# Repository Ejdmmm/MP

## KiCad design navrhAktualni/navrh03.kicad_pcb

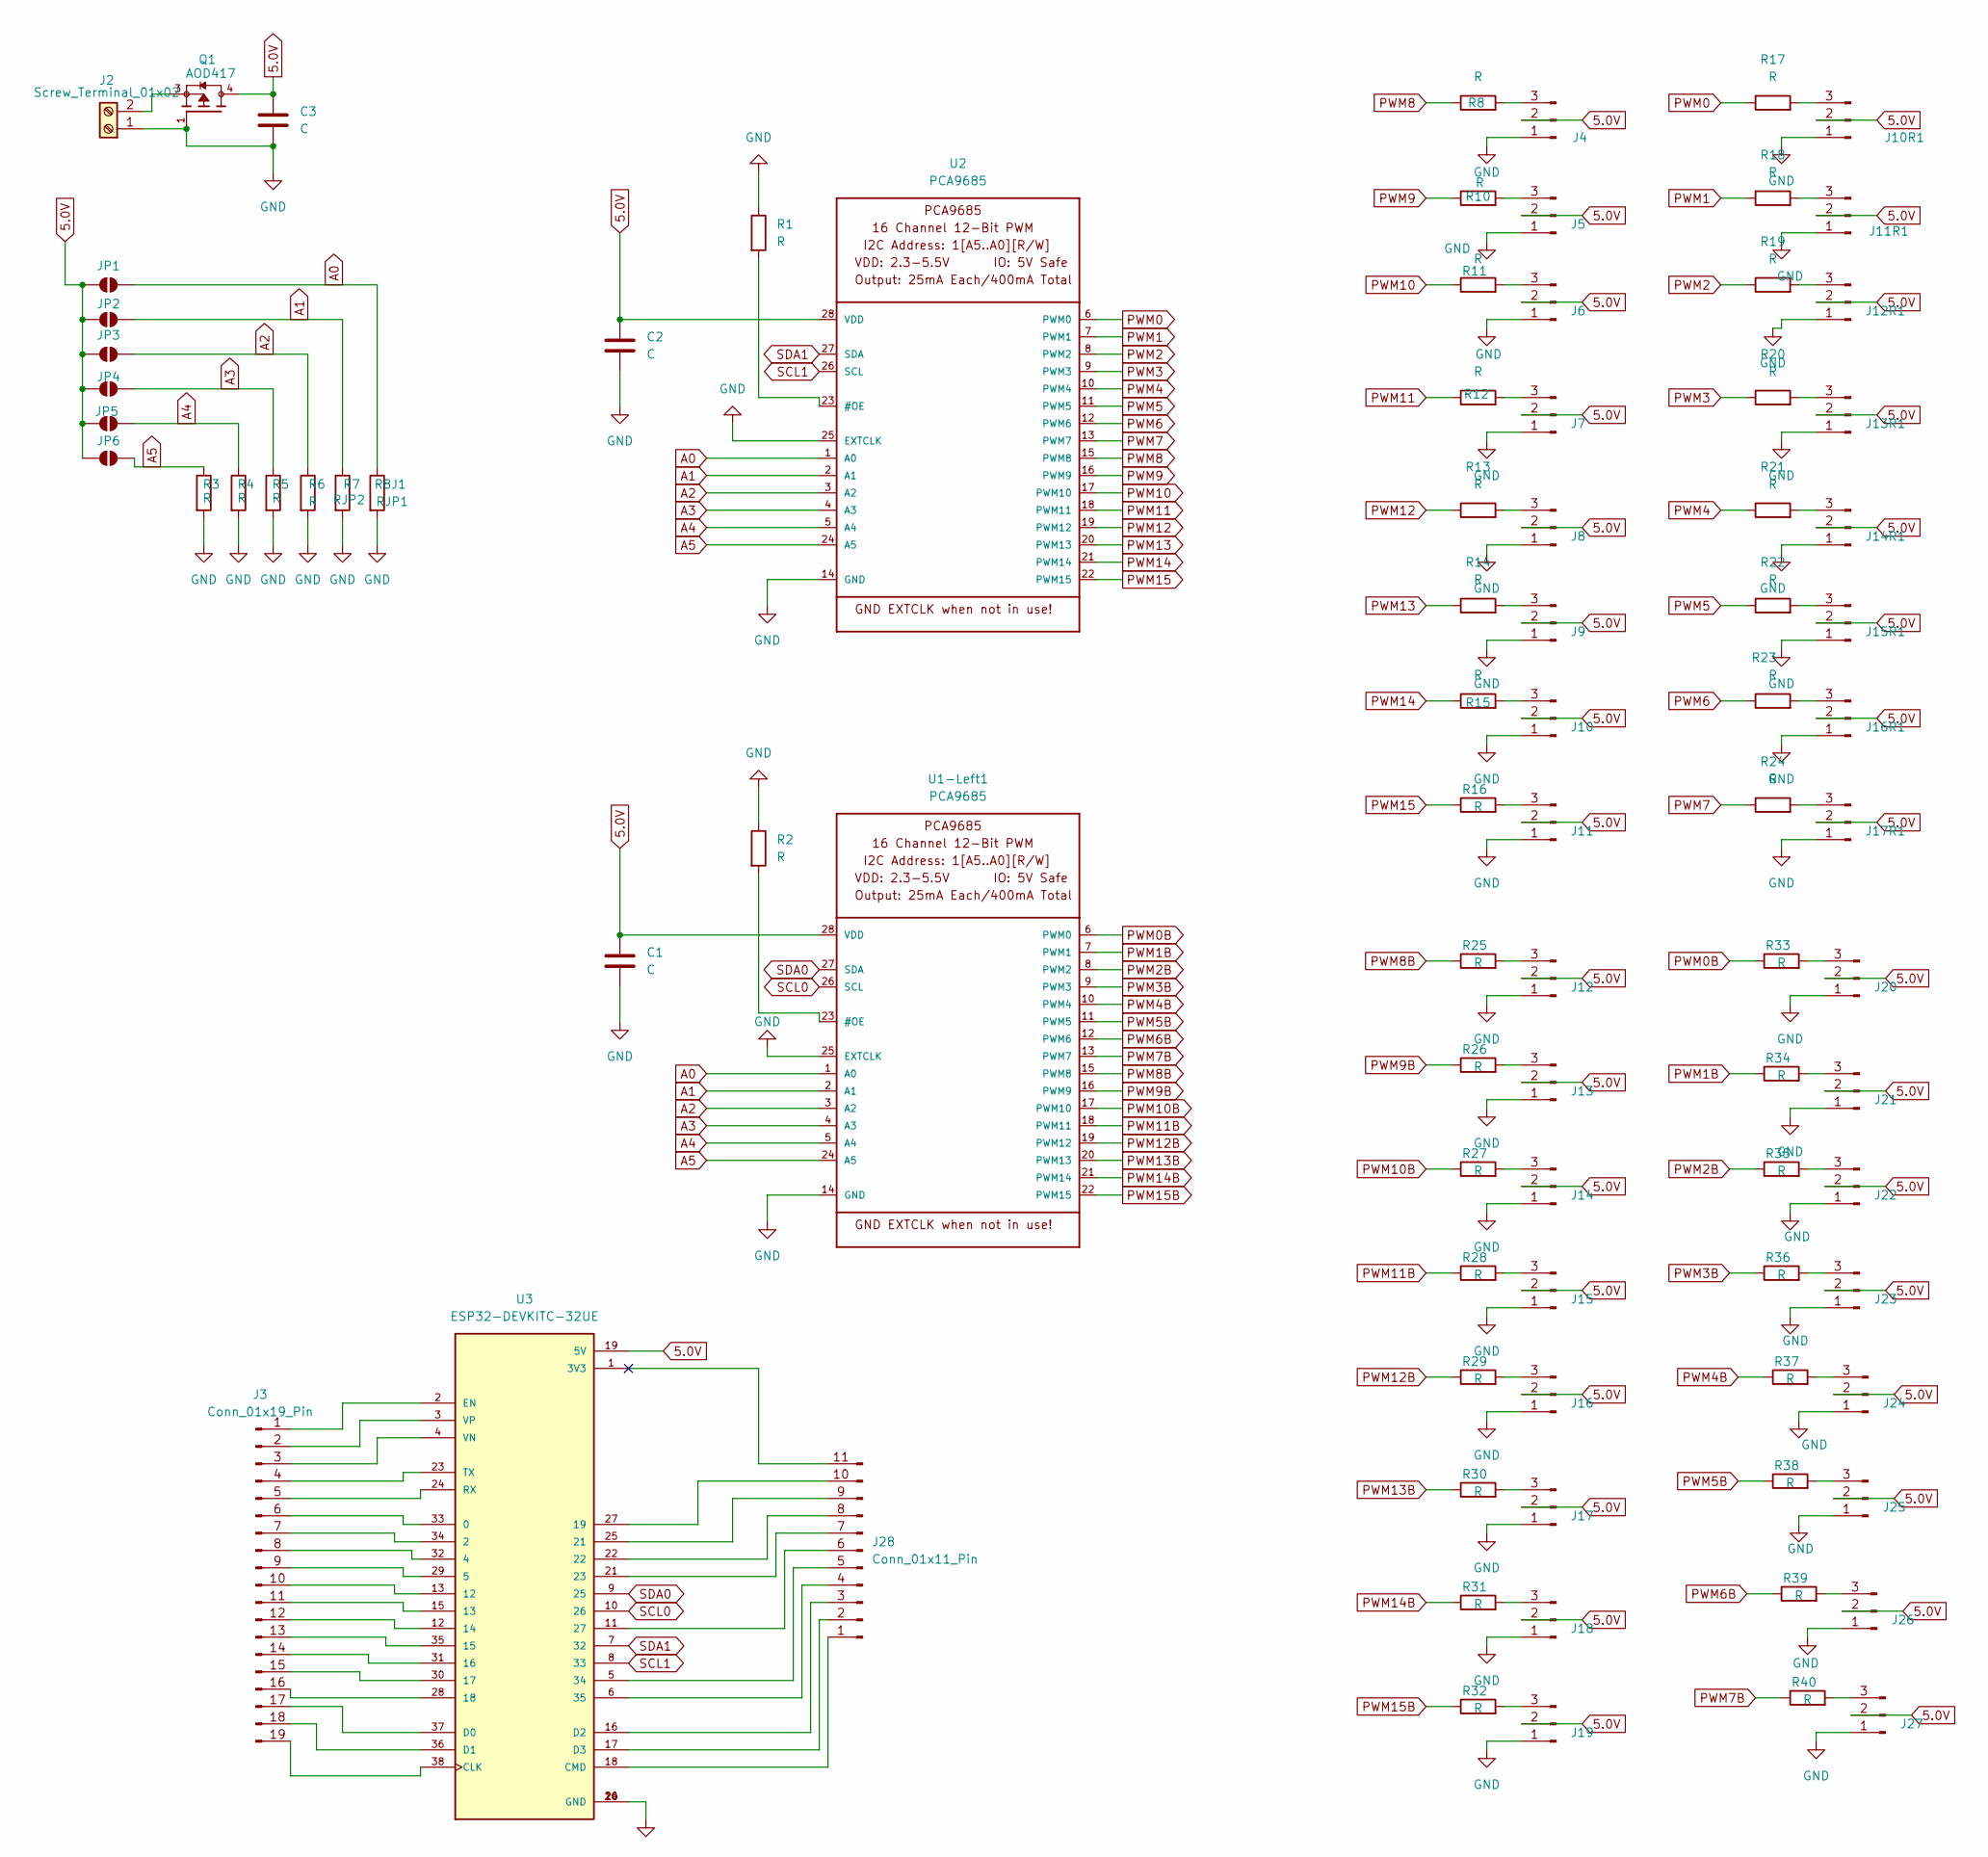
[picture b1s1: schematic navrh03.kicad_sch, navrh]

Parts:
C1: C; C_Disc_D7.5mm_W5.0mm_P7.50mm
C2, C3: C; CP_EIA-1608-08_AVX-J
J2: Screw_Terminal_01x02; PinHeader_1x02_P2.00mm_Vertical
J3: Conn_01x19_Pin; PinHeader_1x19_P2.00mm_Vertical
J4, J5, J6, J7, J8, J9, J10, J10R1, J11, J11R1, J12, J12R1, J13, J13R1, J14, J14R1, J15, J15R1, J16, J16R1, J17, J17R1, J18, J19, J20, J21, J22, J23, J24, J25, J26, J27: Conn_01x03_Pin; PinHeader_1x03_P2.00mm_Vertical
J28: Conn_01x11_Pin; PinHeader_1x11_P2.00mm_Vertical
JP1, JP2, JP3, JP4, JP5, JP6: SolderJumper_2_Open; SolderJumper-2_P1.3mm_Open_Pad1.0x1.5mm
Q1: AOD417; DPAK228P994X240_3N; PARTREV U
R1, R2, R3, R4, R5, R6, R8, R10, R11, R12, R13, R14, R15, R16, R17, R18, R19, R20, R21, R22, R23, R24, R25, R26, R27, R28, R29, R30, R31, R32, R33, R34, R35, R36, R37, R38, R39, R40: R; R_0201_0603Metric
R7: RJP2; R_0201_0603Metric
R8J1: RJP1; R_0201_0603Metric
U1-Left1, U2: PCA9685; TSSOP28
U3: ESP32-DEVKITC-32UE; ESPRESSIF_ESP32-DEVKITC-32UE; PARTREV V4

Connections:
A0: JP1.2 (B), R8J1.1, U1-Left1.1 (A0), U2.1 (A0)
A1: JP2.2 (B), R7.1, U1-Left1.2 (A1), U2.2 (A1)
A2: JP3.2 (B), R6.1, U1-Left1.3 (A2), U2.3 (A2)
A3: JP4.2 (B), R5.1, U1-Left1.4 (A3), U2.4 (A3)
A4: JP5.2 (B), R4.1, U1-Left1.5 (A4), U2.5 (A4)
A5: JP6.2 (B), R3.1, U1-Left1.24 (A5), U2.24 (A5)
unnamed: J2.2, Q1.3
unnamed: J3.1, U3.2 (EN)
unnamed: J3.2, U3.3 (VP)
unnamed: J3.3, U3.4 (VN)
unnamed: J3.4, U3.23 (TX)
unnamed: J3.5, U3.24 (RX)
unnamed: J3.6, U3.33 (0)
unnamed: J3.7, U3.34 (2)
unnamed: J3.8, U3.32 (4)
unnamed: J3.9, U3.29 (5)
unnamed: J3.10, U3.13 (12)
unnamed: J3.11, U3.15 (13)
unnamed: J3.12, U3.12 (14)
unnamed: J3.13, U3.35 (15)
unnamed: J3.14, U3.31 (16)
unnamed: J3.15, U3.30 (17)
unnamed: J3.16, U3.28 (18)
unnamed: J3.17, U3.37 (D0)
unnamed: J3.18, U3.36 (D1)
unnamed: J3.19, U3.38 (CLK)
unnamed: J4.3, R8.2
unnamed: J5.3, R10.2
unnamed: J6.3, R11.2
unnamed: J7.3, R12.2
unnamed: J8.3, R13.2
unnamed: J9.3, R14.2
unnamed: J10.3, R15.2
unnamed: J10R1.3, R17.2
unnamed: J11.3, R16.2
unnamed: J11R1.3, R18.2
unnamed: J12.3, R25.2
unnamed: J12R1.3, R19.2
unnamed: J13.3, R26.2
unnamed: J13R1.3, R20.2
unnamed: J14.3, R27.2
unnamed: J14R1.3, R21.2
unnamed: J15.3, R28.2
unnamed: J15R1.3, R22.2
unnamed: J16.3, R29.2
unnamed: J16R1.3, R23.2
unnamed: J17.3, R30.2
unnamed: J17R1.3, R24.2
unnamed: J18.3, R31.2
unnamed: J19.3, R32.2
unnamed: J20.3, R33.2
unnamed: J21.3, R34.2
unnamed: J22.3, R35.2
unnamed: J23.3, R36.2
unnamed: J24.3, R37.2
unnamed: J25.3, R38.2
unnamed: J26.3, R39.2
unnamed: J27.3, R40.2
unnamed: J28.1, U3.18 (CMD)
unnamed: J28.2, U3.17 (D3)
unnamed: J28.3, U3.16 (D2)
unnamed: J28.4, U3.6 (35)
unnamed: J28.5, U3.5 (34)
unnamed: J28.6, U3.11 (27)
unnamed: J28.7, U3.21 (23)
unnamed: J28.8, U3.22
unnamed: J28.9, U3.25 (21)
unnamed: J28.10, U3.27 (19)
unnamed: R2.2, U1-Left1.23 (#OE)
unnamed: R1.2, U2.23 (#OE)
PWM0: R17.1, U2.6 (PWM0)
PWM0B: R33.1, U1-Left1.6 (PWM0)
PWM1: R18.1, U2.7 (PWM1)
PWM1B: R34.1, U1-Left1.7 (PWM1)
PWM2: R19.1, U2.8 (PWM2)
PWM2B: R35.1, U1-Left1.8 (PWM2)
PWM3: R20.1, U2.9 (PWM3)
PWM3B: R36.1, U1-Left1.9 (PWM3)
PWM4: R21.1, U2.10 (PWM4)
PWM4B: R37.1, U1-Left1.10 (PWM4)
PWM5: R22.1, U2.11 (PWM5)
PWM5B: R38.1, U1-Left1.11 (PWM5)
PWM6: R23.1, U2.12 (PWM6)
PWM6B: R39.1, U1-Left1.12 (PWM6)
PWM7: R24.1, U2.13 (PWM7)
PWM7B: R40.1, U1-Left1.13 (PWM7)
PWM8: R8.1, U2.15 (PWM8)
PWM8B: R25.1, U1-Left1.15 (PWM8)
PWM9: R10.1, U2.16 (PWM9)
PWM9B: R26.1, U1-Left1.16 (PWM9)
PWM10: R11.1, U2.17 (PWM10)
PWM10B: R27.1, U1-Left1.17 (PWM10)
PWM11: R12.1, U2.18 (PWM11)
PWM11B: R28.1, U1-Left1.18 (PWM11)
PWM12: R13.1, U2.19 (PWM12)
PWM12B: R29.1, U1-Left1.19 (PWM12)
PWM13: R14.1, U2.20 (PWM13)
PWM13B: R30.1, U1-Left1.20 (PWM13)
PWM14: R15.1, U2.21 (PWM14)
PWM14B: R31.1, U1-Left1.21 (PWM14)
PWM15: R16.1, U2.22 (PWM15)
PWM15B: R32.1, U1-Left1.22 (PWM15)
SCL0: U1-Left1.26 (SCL), U3.10 (26)
SCL1: U2.26 (SCL), U3.8 (33)
SDA0: U1-Left1.27 (SDA), U3.9 (25)
SDA1: U2.27 (SDA), U3.7 (32)

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
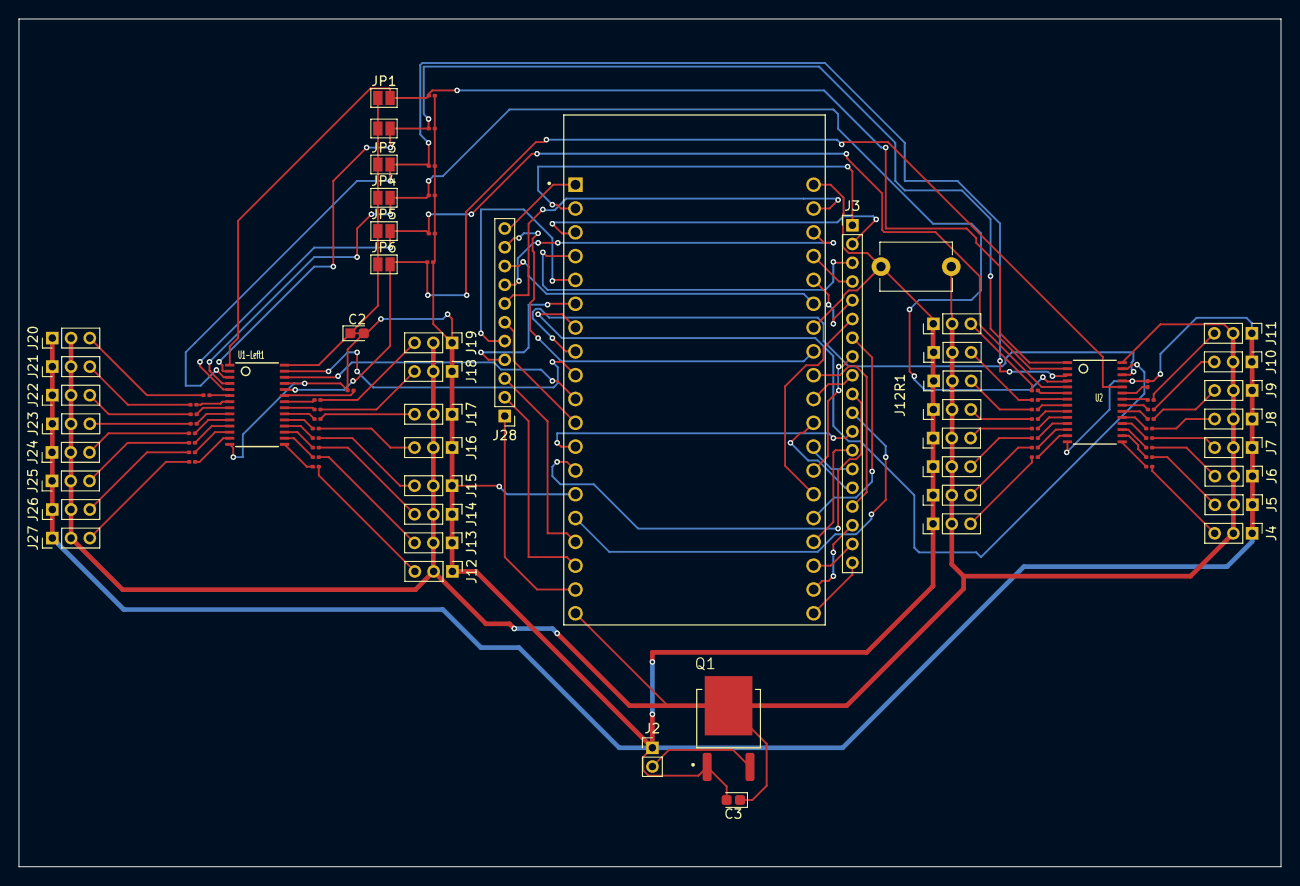
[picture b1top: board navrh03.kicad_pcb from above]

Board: 2 copper layers, 134.6 x 90.4 mm, 88 parts (0 on the bottom side), 108 nets.

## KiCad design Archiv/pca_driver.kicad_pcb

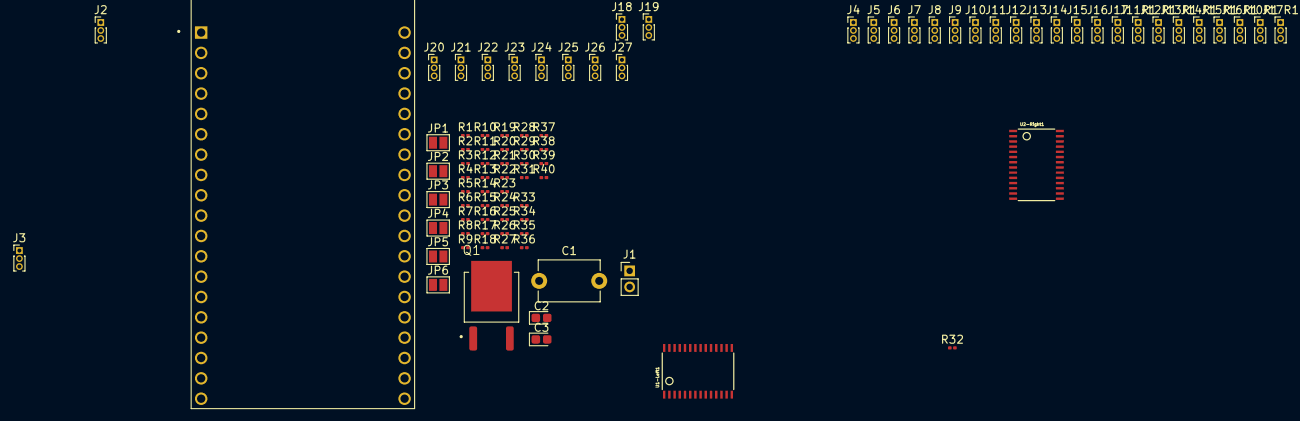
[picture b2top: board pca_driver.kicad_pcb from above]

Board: 2 copper layers, 88 parts (0 on the bottom side), 85 nets, no tracks yet.

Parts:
C1: C_Polarized_US; C_Disc_D7.5mm_W5.0mm_P7.50mm
C2, C3: C; CP_EIA-1608-08_AVX-J
J1: Screw_Terminal_01x02; PinHeader_1x02_P2.00mm_Vertical
J2: Conn_01x19_Pin; PinHeader_1x03_P1.00mm_Vertical
J3: Conn_01x11_Pin; PinHeader_1x03_P1.00mm_Vertical
J4, J5, J6, J7, J8, J9, J10, J10R1, J11, J11R1, J12, J12R1, J13, J13R1, J14, J14R1, J15, J15R1, J16, J16R1, J17, J17R1, J18, J19, J20, J21, J22, J23, J24, J25, J26, J27: PinHeader_1x03_P1.00mm_Vertical
JP1, JP2, JP3, JP4, JP5, JP6: SolderJumper-2_P1.3mm_Open_Pad1.0x1.5mm
Q1: AOD417; DPAK228P994X240_3N
R1, R2, R3, R4, R5, R6, R7, R8, R9, R10, R11, R12, R13, R14, R15, R16, R17, R18, R19, R20, R21, R22, R23, R24, R25, R26, R27, R28, R29, R30, R31, R32, R33, R34, R35, R36, R37, R38, R39, R40: R; R_0201_0603Metric
U1: ESP32-DEVKITC-32UE; ESPRESSIF_ESP32-DEVKITC-32UE
U1-Left1, U2-Right1: PCA9685; TSSOP28

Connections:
5.0V: C1.1, C2.1, C3.1, J4.2, J5.2, J6.2, J7.2, J8.2, J9.2, J10.2, J10R1.2, J11.2, J11R1.2, J12.2, J12R1.2, J13.2, J13R1.2, J14.2, J14R1.2, J15.2, J15R1.2, J16.2, J16R1.2, J17.2, J17R1.2, J18.2, J19.2, J20.2, J21.2, J22.2, J23.2, J24.2, J25.2, J26.2, J27.2, JP1.1 (A), JP2.1 (A), JP3.1 (A), JP4.1 (A), JP5.1 (A), JP6.1 (A), Q1.3, U1.19 (5V), U1-Left1.28 (VDD), U2-Right1.28 (VDD)
A0: JP1.2 (B), R6.1, U1-Left1.1 (A0), U2-Right1.1 (A0)
A1: JP2.2 (B), R5.1, U1-Left1.2 (A1), U2-Right1.2 (A1)
A2: JP3.2 (B), R4.1, U1-Left1.3 (A2), U2-Right1.3 (A2)
A3: JP4.2 (B), R3.1, U1-Left1.4 (A3), U2-Right1.4 (A3)
A4: JP5.2 (B), R2.1, U1-Left1.5 (A4), U2-Right1.5 (A4)
A5: JP6.2 (B), R1.1, U1-Left1.24 (A5), U2-Right1.24 (A5)
GND: C1.2, C2.2, C3.2, J1.1, J4.1, J5.1, J6.1, J7.1, J8.1, J9.1, J10.1, J10R1.1, J11.1, J11R1.1, J12.1, J12R1.1, J13.1, J13R1.1, J14.1, J14R1.1, J15.1, J15R1.1, J16.1, J16R1.1, J17.1, J17R1.1, J18.1, J19.1, J20.1, J21.1, J22.1, J23.1, J24.1, J25.1, J26.1, J27.1, Q1.1, R1.2, R2.2, R3.2, R4.2, R5.2, R6.2, R7.1, R8.1, U1.14 (GND), U1.20 (GND), U1.26 (GND), U1-Left1.14 (GND), U1-Left1.25 (EXTCLK), U2-Right1.14 (GND), U2-Right1.25 (EXTCLK)
unnamed: J1.2, Q1.4
unnamed: J2.1, U1.2 (EN)
unnamed: J2.2, U1.3 (VP)
unnamed: J2.3, U1.4 (VN)
unnamed: J3.1, U1.18 (CMD)
unnamed: J3.2, U1.17 (D3)
unnamed: J3.3, U1.16 (D2)
unnamed: J4.3, R9.2
unnamed: J5.3, R10.2
unnamed: J6.3, R11.2
unnamed: J7.3, R12.2
unnamed: J8.3, R13.2
unnamed: J9.3, R14.2
unnamed: J10.3, R15.2
unnamed: J10R1.3, R25.2
unnamed: J11.3, R16.2
unnamed: J11R1.3, R26.2
unnamed: J12.3, R17.2
unnamed: J12R1.3, R27.2
unnamed: J13.3, R18.2
unnamed: J13R1.3, R28.2
unnamed: J14.3, R19.2
unnamed: J14R1.3, R29.2
unnamed: J15.3, R20.2
unnamed: J15R1.3, R30.2
unnamed: J16.3, R21.2
unnamed: J16R1.3, R31.2
unnamed: J17.3, R22.2
unnamed: J17R1.3, R32.2
unnamed: J18.3, R23.2
unnamed: J19.3, R24.2
unnamed: J20.3, R33.2
unnamed: J21.3, R34.2
unnamed: J22.3, R35.2
unnamed: J23.3, R36.2
unnamed: J24.3, R37.2
unnamed: J25.3, R38.2
unnamed: J26.3, R39.2
unnamed: J27.3, R40.2
unnamed: R8.2, U1-Left1.23 (#OE)
unnamed: R7.2, U2-Right1.23 (#OE)
PWM0: R25.1, U2-Right1.6 (PWM0)
PWM0B: R33.1, U1-Left1.6 (PWM0)
PWM1: R26.1, U2-Right1.7 (PWM1)
PWM1B: R34.1, U1-Left1.7 (PWM1)
PWM2: R27.1, U2-Right1.8 (PWM2)
PWM2B: R35.1, U1-Left1.8 (PWM2)
PWM3: R28.1, U2-Right1.9 (PWM3)
PWM3B: R36.1, U1-Left1.9 (PWM3)
PWM4: R29.1, U2-Right1.10 (PWM4)
PWM4B: R37.1, U1-Left1.10 (PWM4)
PWM5: R30.1, U2-Right1.11 (PWM5)
PWM5B: R38.1, U1-Left1.11 (PWM5)
PWM6: R31.1, U2-Right1.12 (PWM6)
PWM6B: R39.1, U1-Left1.12 (PWM6)
PWM7: R32.1, U2-Right1.13 (PWM7)
PWM7B: R40.1, U1-Left1.13 (PWM7)
PWM8: R9.1, U2-Right1.15 (PWM8)
PWM8B: R17.1, U1-Left1.15 (PWM8)
PWM9: R10.1, U2-Right1.16 (PWM9)
PWM9B: R18.1, U1-Left1.16 (PWM9)
PWM10: R11.1, U2-Right1.17 (PWM10)
PWM10B: R19.1, U1-Left1.17 (PWM10)
PWM11: R12.1, U2-Right1.18 (PWM11)
PWM11B: R20.1, U1-Left1.18 (PWM11)
PWM12: R13.1, U2-Right1.19 (PWM12)
PWM12B: R21.1, U1-Left1.19 (PWM12)
PWM13: R14.1, U2-Right1.20 (PWM13)
PWM13B: R22.1, U1-Left1.20 (PWM13)
PWM14: R15.1, U2-Right1.21 (PWM14)
PWM14B: R23.1, U1-Left1.21 (PWM14)
PWM15: R16.1, U2-Right1.22 (PWM15)
PWM15B: R24.1, U1-Left1.22 (PWM15)
SCL0: U1.10 (26), U2-Right1.26 (SCL)
SCL1: U1.8 (33), U1-Left1.26 (SCL)
SDA0: U1.9 (25), U2-Right1.27 (SDA)
SDA1: U1.7 (32), U1-Left1.27 (SDA)

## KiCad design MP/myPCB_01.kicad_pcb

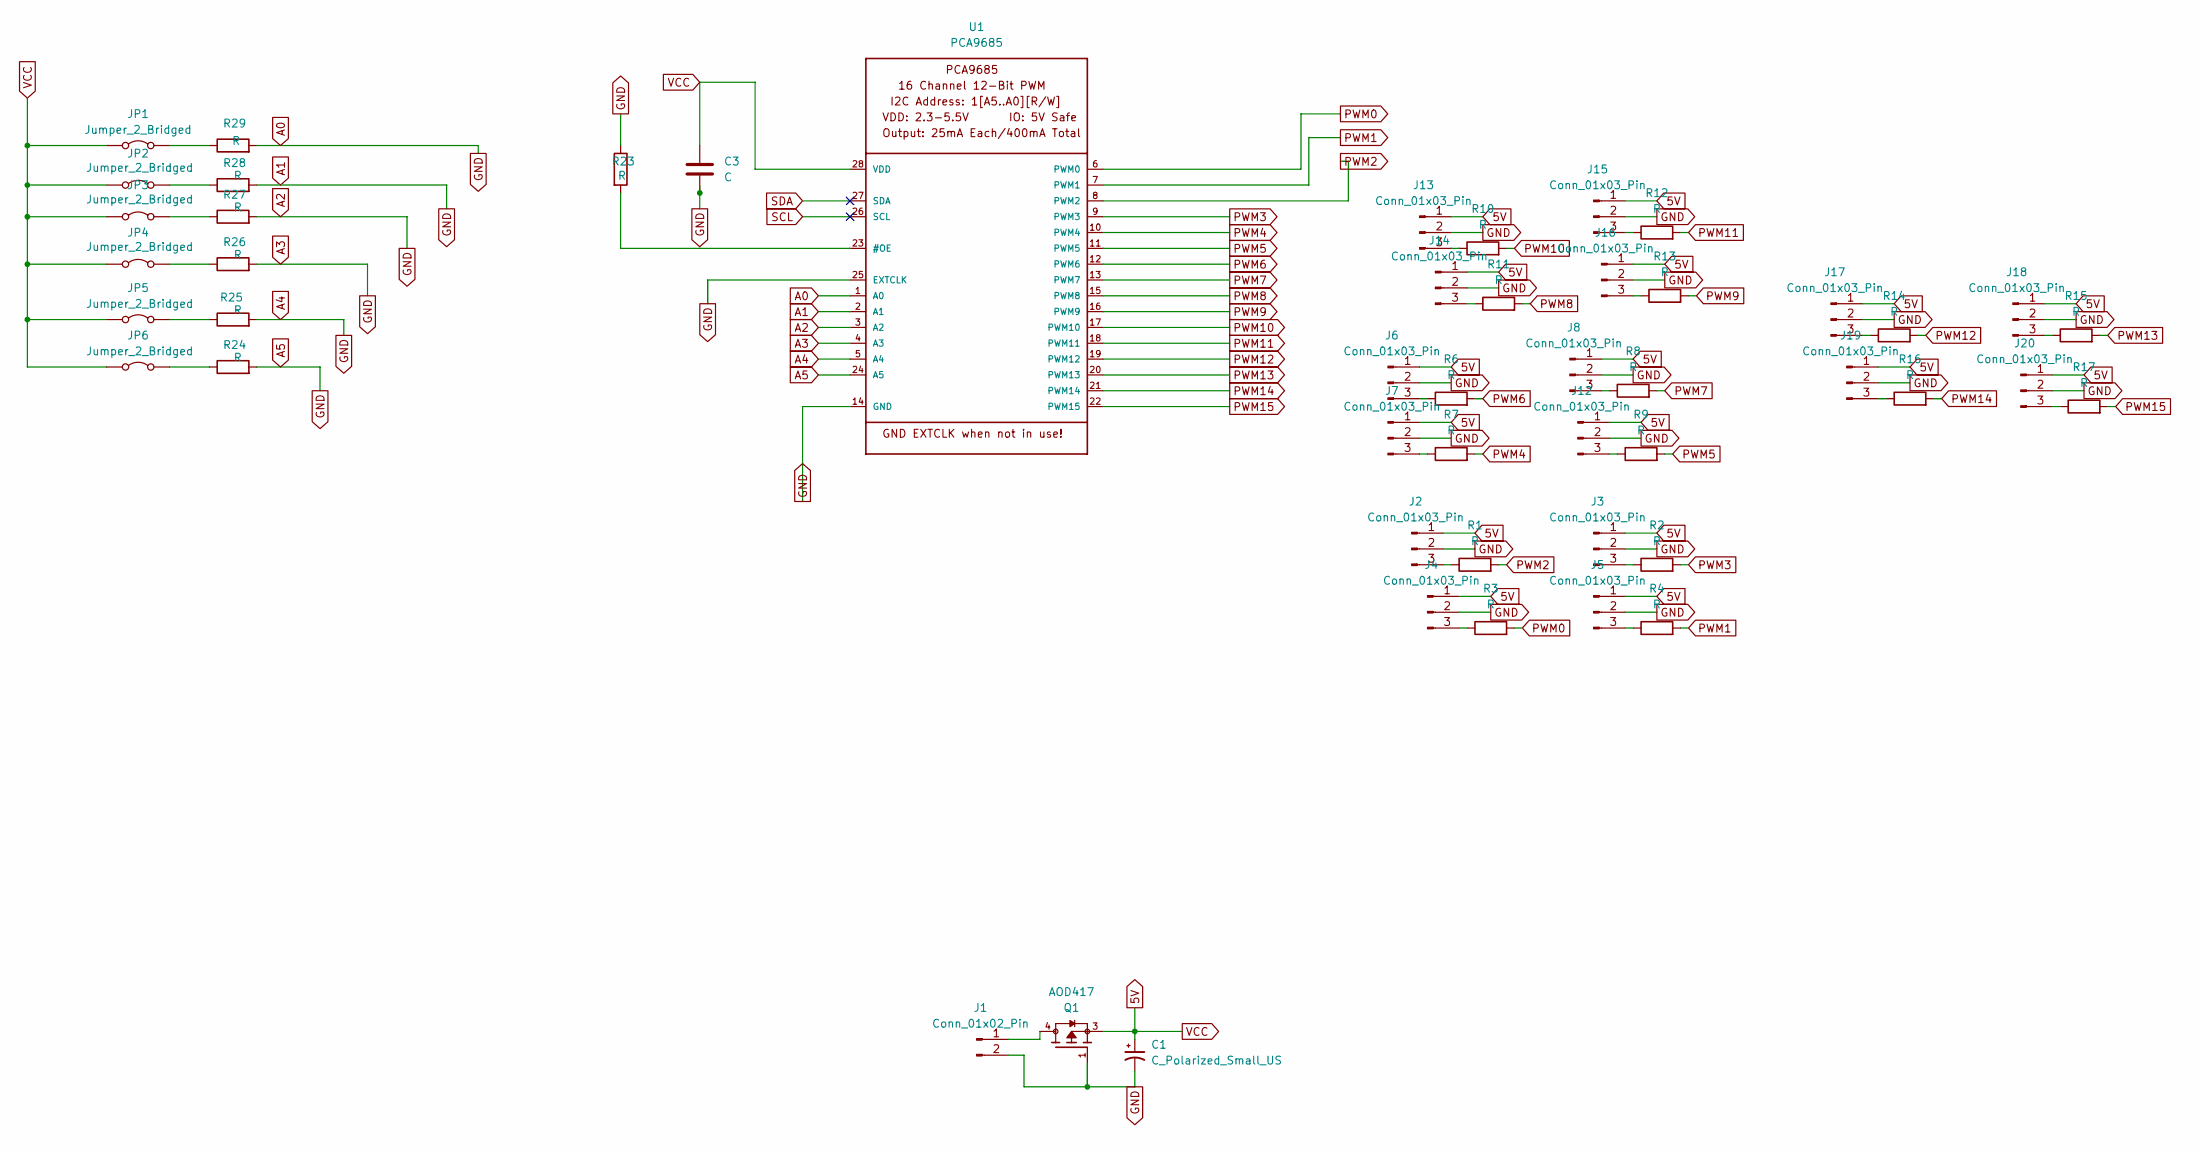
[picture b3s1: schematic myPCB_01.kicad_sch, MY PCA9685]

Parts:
C1: C_Polarized_Small_US; CP_Radial_D7.5mm_P2.50mm
C3: C; CP_Axial_L10.0mm_D4.5mm_P15.00mm_Horizontal
J1: Conn_01x02_Pin; PinHeader_1x02_P1.00mm_Vertical
J2, J3, J4, J5, J6, J7, J8, J12, J13, J14, J15, J16, J17, J18, J19, J20: Conn_01x03_Pin; PinHeader_1x03_P2.00mm_Vertical
JP1, JP2, JP3, JP4, JP5, JP6: Jumper_2_Bridged; SolderJumper-2_P1.3mm_Bridged2Bar_Pad1.0x1.5mm
Q1: AOD417; DPAK228P994X240_3N; PARTREV U
R1, R2, R3, R4, R6, R7, R8, R9, R10, R11, R12, R13, R14, R15, R16, R17, R23, R24, R25, R26, R27, R28, R29: R; R_0201_0603Metric
U1: PCA9685; TSSOP28

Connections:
5V: C1.1, C3.1, J2.1, J3.1, J4.1, J5.1, J6.1, J7.1, J8.1, J12.1, J13.1, J14.1, J15.1, J16.1, J17.1, J18.1, J19.1, J20.1, JP1.1 (A), JP2.1 (A), JP3.1 (A), JP4.1 (A), JP5.1 (A), JP6.1 (A), Q1.3, U1.28 (VDD)
A0: C1.2, C3.2, J1.2, J2.2, J3.2, J4.2, J5.2, J6.2, J7.2, J8.2, J12.2, J13.2, J14.2, J15.2, J16.2, J17.2, J18.2, J19.2, J20.2, Q1.1, R23.1, R24.2, R25.2, R26.2, R27.2, R28.2, R29.2, U1.1 (A0), U1.2 (A1), U1.3 (A2), U1.4 (A3), U1.5 (A4), U1.14 (GND), U1.24 (A5), U1.25 (EXTCLK)
unnamed: J1.1, Q1.4
unnamed: J2.3, R1.1
unnamed: J3.3, R2.1
unnamed: J4.3, R3.1
unnamed: J5.3, R4.1
unnamed: J6.3, R6.1
unnamed: J7.3, R7.1
unnamed: J8.3, R8.1
unnamed: J12.3, R9.1
unnamed: J13.3, R10.1
unnamed: J14.3, R11.1
unnamed: J15.3, R12.1
unnamed: J16.3, R13.1
unnamed: J17.3, R14.1
unnamed: J18.3, R15.1
unnamed: J19.3, R16.1
unnamed: J20.3, R17.1
unnamed: JP1.2 (B), R29.1
unnamed: JP2.2 (B), R28.1
unnamed: JP3.2 (B), R27.1
unnamed: JP4.2 (B), R26.1
unnamed: JP5.2 (B), R25.1
unnamed: JP6.2 (B), R24.1
unnamed: R23.2, U1.23 (#OE)
PWM0: R3.2, U1.6 (PWM0)
PWM1: R4.2, U1.7 (PWM1)
PWM2: R1.2, U1.8 (PWM2)
PWM3: R2.2, U1.9 (PWM3)
PWM4: R7.2, U1.10 (PWM4)
PWM5: R9.2, U1.11 (PWM5)
PWM6: R6.2, U1.12 (PWM6)
PWM7: R8.2, U1.13 (PWM7)
PWM8: R11.2, U1.15 (PWM8)
PWM9: R13.2, U1.16 (PWM9)
PWM10: R10.2, U1.17 (PWM10)
PWM11: R12.2, U1.18 (PWM11)
PWM12: R14.2, U1.19 (PWM12)
PWM13: R15.2, U1.20 (PWM13)
PWM14: R16.2, U1.21 (PWM14)
PWM15: R17.2, U1.22 (PWM15)
SCL: U1.26 (SCL)
SDA: U1.27 (SDA)

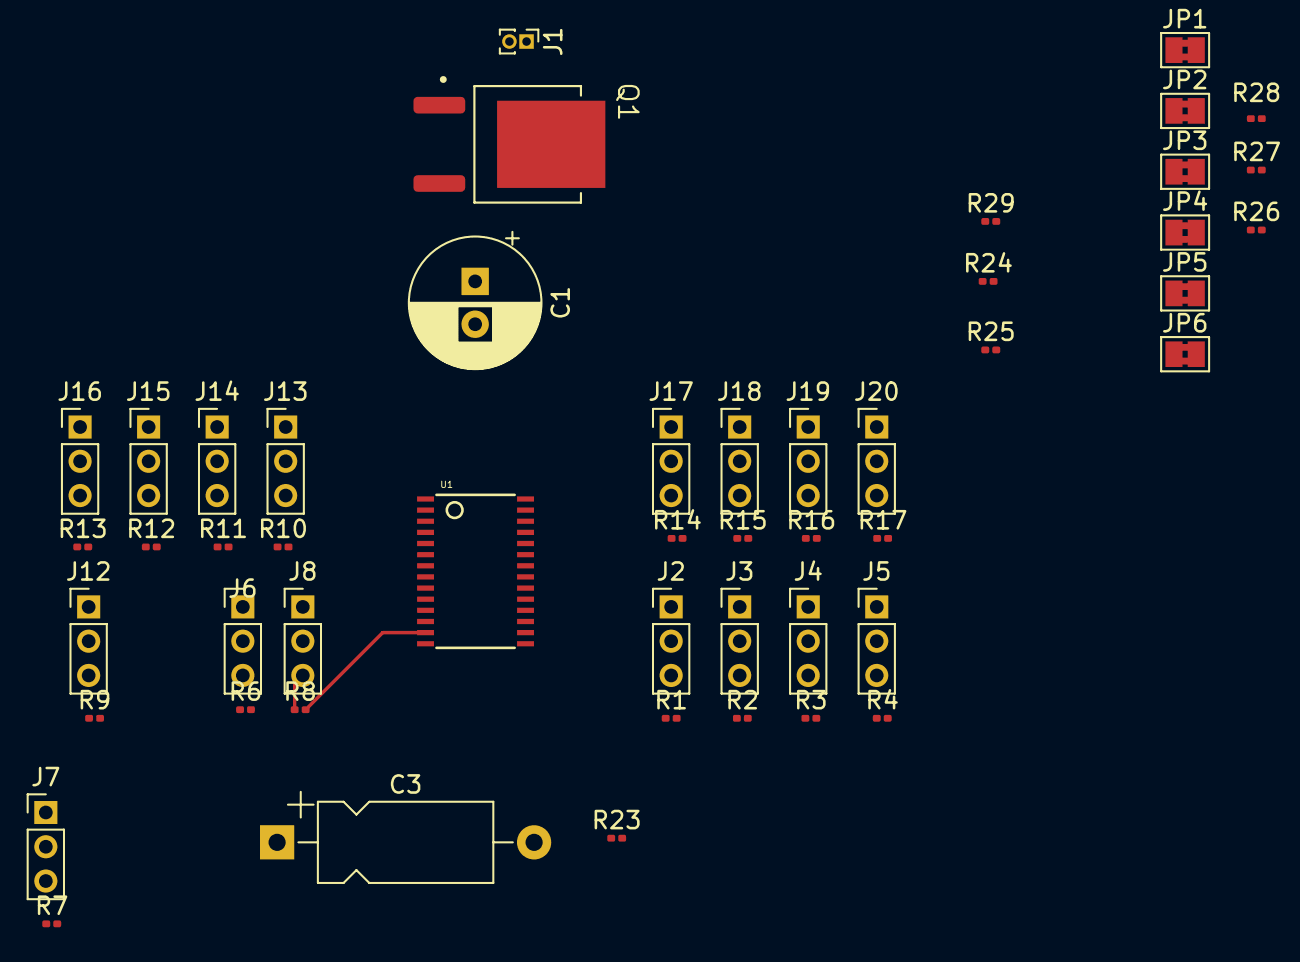
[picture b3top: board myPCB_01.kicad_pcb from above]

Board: 2 copper layers, 50 parts (0 on the bottom side), 42 nets.

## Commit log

2024-11-06 dokumentace, fotky k mp
2024-11-06 navrh&wiring
2024-11-08 Add files via upload
    Try to wire jumpers etc.
2024-11-24 NavrhMP check
